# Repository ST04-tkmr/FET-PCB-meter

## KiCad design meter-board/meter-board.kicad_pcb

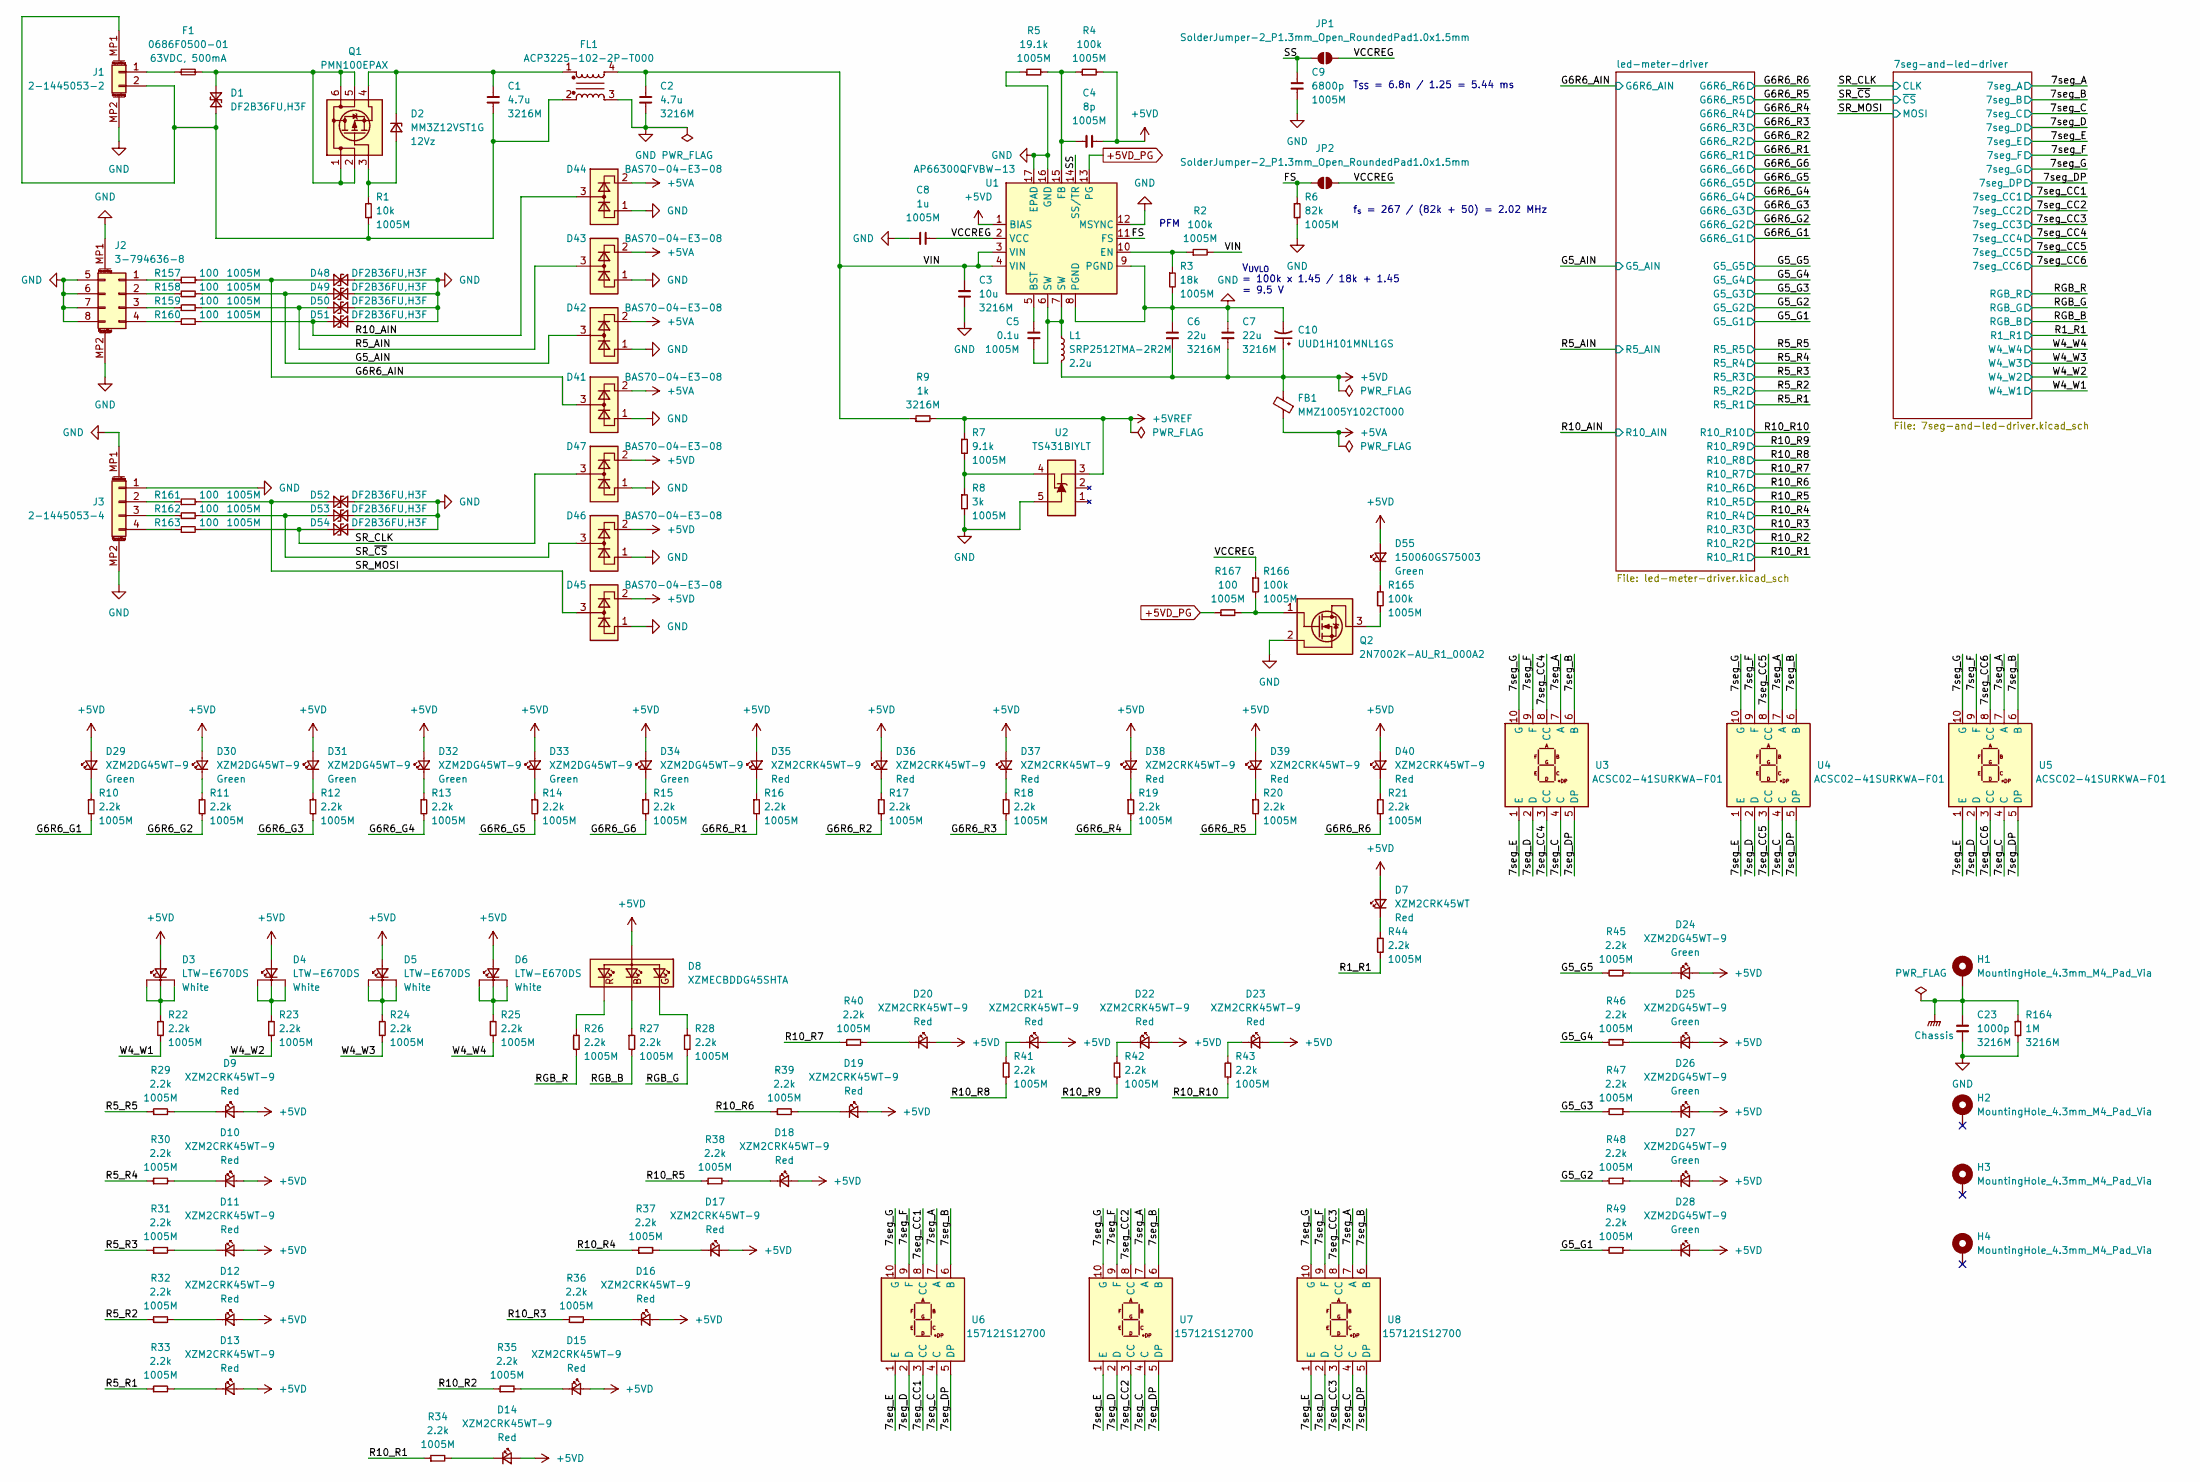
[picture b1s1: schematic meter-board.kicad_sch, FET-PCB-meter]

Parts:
C1, C2: 4.7u; C_1206_3216M
C3: 10u; C_1206_3216M
C4: 8p; C_0402_1005M
C5: 0.1u; C_0402_1005M
C6, C7: 22u; C_1206_3216M
C8: 1u; C_0402_1005M
C9: 6800p; C_0402_1005M
C10: UUD1H101MNL1GS; DigikeyPN 493-2306-1-ND
C23: 1000p; C_1206_3216M
D1, D48, D49, D50, D51, D52, D53, D54: DF2B36FU,H3F; DigikeyPN DF2B36FUH3FCT-ND
D2: MM3Z12VST1G; DigikeyPN MM3Z12VST1GOSCT-ND
D3, D4, D5, D6: LTW-E670DS; DigikeyPN 160-1766-1-ND
D7: XZM2CRK45WT; DigikeyPN 1497-1322-1-ND
D8: XZMECBDDG45SHTA; DigikeyPN 1497-XZMECBDDG45SHTACT-ND
D9, D10, D11, D12, D13, D14, D15, D16, D17, D18, D19, D20, D21, D22, D23, D35, D36, D37, D38, D39, D40: XZM2CRK45WT-9; DigikeyPN 1497-1332-1-ND
D24, D25, D26, D27, D28, D29, D30, D31, D32, D33, D34: XZM2DG45WT-9; DigikeyPN 1497-1338-1-ND
D41, D42, D43, D44, D45, D46, D47: BAS70-04-E3-08; DigikeyPN BAS70-04-E3-08CT-ND
D55: 150060GS75003; DigikeyPN 732-150060GS75003CT-ND
F1: 0686F0500-01; DigikeyPN 5923-0686F0500-01CT-ND
FB1: MMZ1005Y102CT000; DigikeyPN 445-2157-1-ND
FL1: ACP3225-102-2P-T000; DigikeyPN 445-8637-1-ND
H1, H2, H3, H4: MountingHole_4.3mm_M4_Pad_Via
J1: 2-1445053-2; DigikeyPN A33199CT-ND
J2: 3-794636-8; DigikeyPN A33238CT-ND
J3: 2-1445053-4; DigikeyPN A33201CT-ND
JP1, JP2: SolderJumper-2_P1.3mm_Open_RoundedPad1.0x1.5mm
L1: SRP2512TMA-2R2M; DigikeyPN 118-SRP2512TMA-2R2MCT-ND
Q1: PMN100EPAX; DigikeyPN 1727-PMN100EPAXCT-ND
Q2: 2N7002K-AU_R1_000A2; DigikeyPN 3757-2N7002K-AU_R1_000A2CT-ND
R1: 10k; R_0402_1005M
R2, R4, R165, R166: 100k; R_0402_1005M
R3: 18k; R_0402_1005M
R5: 19.1k; R_0402_1005M
R6: 82k; R_0402_1005M
R7: 9.1k; R_0402_1005M
R8: 3k; R_0402_1005M
R9: 1k; R_1206_3216M
R10, R11, R12, R13, R14, R15, R16, R17, R18, R19, R20, R21, R22, R23, R24, R25, R26, R27, R28, R29, R30, R31, R32, R33, R34, R35, R36, R37, R38, R39, R40, R41, R42, R43, R44, R45, R46, R47, R48, R49: 2.2k; R_0402_1005M
R157, R158, R159, R160, R161, R162, R163, R167: 100; R_0402_1005M
R164: 1M; R_1206_3216M
U1: AP66300QFVBW-13; DigikeyPN 31-AP66300QFVBW-13CT-ND
U2: TS431BIYLT; DigikeyPN 497-10248-1-ND
U3, U4, U5: ACSC02-41SURKWA-F01; DigikeyPN 754-1405-1-ND
U6, U7, U8: 157121S12700; DigikeyPN 732-157121S12700CT-ND

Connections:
+5VA: D41.2 (K), D42.2 (K), D43.2 (K), D44.2 (K), FB1.1; also elsewhere on the board
+5VD: C4.2, C6.2, C7.2, C10.1, D3.2 (A), D4.2 (A), D5.2 (A), D6.2 (A), D7.1 (A), D8.2 (A), D9.2 (A), D10.2 (A), D11.2 (A), D12.2 (A), D13.2 (A), D14.2 (A), D15.2 (A), D16.2 (A), D17.2 (A), D18.2 (A), D19.2 (A), D20.2 (A), D21.2 (A), D22.2 (A), D23.2 (A), D24.1 (A), D25.1 (A), D26.1 (A), D27.1 (A), D28.1 (A), D29.1 (A), D30.1 (A), D31.1 (A), D32.1 (A), D33.1 (A), D34.1 (A), D35.2 (A), D36.2 (A), D37.2 (A), D38.2 (A), D39.2 (A), D40.2 (A), D45.2 (K), D46.2 (K), D47.2 (K), D55.1 (A), FB1.2, L1.2, R4.2, U1.1 (BIAS); also elsewhere on the board
+5VD_PG: R167.1, U1.13 (PG)
+5VREF: R7.1, R9.2, U2.3 (K); also elsewhere on the board
/7seg_A: U3.7 (A), U4.7 (A), U5.7 (A), U6.7 (A), U7.7 (A), U8.7 (A); also elsewhere on the board
/7seg_B: U3.6 (B), U4.6 (B), U5.6 (B), U6.6 (B), U7.6 (B), U8.6 (B); also elsewhere on the board
/7seg_C: U3.4 (C), U4.4 (C), U5.4 (C), U6.4 (C), U7.4 (C), U8.4 (C); also elsewhere on the board
/7seg_CC1: U6.3 (CC), U6.8 (CC); also elsewhere on the board
/7seg_CC2: U7.3 (CC), U7.8 (CC); also elsewhere on the board
/7seg_CC3: U8.3 (CC), U8.8 (CC); also elsewhere on the board
/7seg_CC4: U3.3 (CC), U3.8 (CC); also elsewhere on the board
/7seg_CC5: U4.3 (CC), U4.8 (CC); also elsewhere on the board
/7seg_CC6: U5.3 (CC), U5.8 (CC); also elsewhere on the board
/7seg_D: U3.2 (D), U4.2 (D), U5.2 (D), U6.2 (D), U7.2 (D), U8.2 (D); also elsewhere on the board
/7seg_DP: U3.5 (DP), U4.5 (DP), U5.5 (DP), U6.5 (DP), U7.5 (DP), U8.5 (DP); also elsewhere on the board
/7seg_E: U3.1 (E), U4.1 (E), U5.1 (E), U6.1 (E), U7.1 (E), U8.1 (E); also elsewhere on the board
/7seg_F: U3.9 (F), U4.9 (F), U5.9 (F), U6.9 (F), U7.9 (F), U8.9 (F); also elsewhere on the board
/7seg_G: U3.10 (G), U4.10 (G), U5.10 (G), U6.10 (G), U7.10 (G), U8.10 (G); also elsewhere on the board
/FS: JP2.1 (A), R6.1, U1.11 (FS)
/G5_AIN: D42.3 (C), D49.1 (A1), R158.2; also elsewhere on the board
/G5_G1: R49.2; also elsewhere on the board
/G5_G2: R48.2; also elsewhere on the board
/G5_G3: R47.2; also elsewhere on the board
/G5_G4: R46.2; also elsewhere on the board
/G5_G5: R45.2; also elsewhere on the board
/G6R6_AIN: D41.3 (C), D48.1 (A1), R157.2; also elsewhere on the board
/G6R6_G1: R10.2; also elsewhere on the board
/G6R6_G2: R11.2; also elsewhere on the board
/G6R6_G3: R12.2; also elsewhere on the board
/G6R6_G4: R13.2; also elsewhere on the board
/G6R6_G5: R14.2; also elsewhere on the board
/G6R6_G6: R15.2; also elsewhere on the board
/G6R6_R1: R16.2; also elsewhere on the board
/G6R6_R2: R17.2; also elsewhere on the board
/G6R6_R3: R18.2; also elsewhere on the board
/G6R6_R4: R19.2; also elsewhere on the board
/G6R6_R5: R20.2; also elsewhere on the board
/G6R6_R6: R21.2; also elsewhere on the board
/R1_R1: R44.2; also elsewhere on the board
/R5_AIN: D43.3 (C), D50.1 (A1), R159.2; also elsewhere on the board
/R5_R1: R33.1; also elsewhere on the board
/R5_R2: R32.1; also elsewhere on the board
/R5_R3: R31.1; also elsewhere on the board
/R5_R4: R30.1; also elsewhere on the board
/R5_R5: R29.1; also elsewhere on the board
/R10_AIN: D44.3 (C), D51.1 (A1), R160.2; also elsewhere on the board
/R10_R1: R34.1; also elsewhere on the board
/R10_R2: R35.1; also elsewhere on the board
/R10_R3: R36.1; also elsewhere on the board
/R10_R4: R37.1; also elsewhere on the board
/R10_R5: R38.1; also elsewhere on the board
/R10_R6: R39.1; also elsewhere on the board
/R10_R7: R40.1; also elsewhere on the board
/R10_R8: R41.1; also elsewhere on the board
/R10_R9: R42.1; also elsewhere on the board
/R10_R10: R43.1; also elsewhere on the board
/RGB_B: R27.2; also elsewhere on the board
/RGB_G: R28.2; also elsewhere on the board
/RGB_R: R26.2; also elsewhere on the board
/SR_CLK: D47.3 (C), D54.1 (A1), R163.2; also elsewhere on the board
/SR_MOSI: D45.3 (C), D52.1 (A1), R161.2; also elsewhere on the board
/SR_~CS: D46.3 (C), D53.1 (A1), R162.2; also elsewhere on the board
/SS: C9.2, JP1.1 (A), U1.14 (SS/TR)
/VCCREG: C8.2, JP1.2 (B), JP2.2 (B), R166.1, U1.2 (VCC)
/VIN: C2.1, C3.1, FL1.4, R2.2, R9.1, U1.3 (VIN), U1.4 (VIN)
/W4_W1: R22.2; also elsewhere on the board
/W4_W2: R23.2; also elsewhere on the board
/W4_W3: R24.2; also elsewhere on the board
/W4_W4: R25.2; also elsewhere on the board
Chassis: C23.1, H1.MP, R164.1
GND: C2.2, C3.2, C6.1, C7.1, C8.1, C9.1, C10.2, C23.2, D41.1 (A), D42.1 (A), D43.1 (A), D44.1 (A), D45.1 (A), D46.1 (A), D47.1 (A), D48.2 (A2), D49.2 (A2), D50.2 (A2), D51.2 (A2), D52.2 (A2), D53.2 (A2), D54.2 (A2), FL1.3, J1.MP2 (MountPin), J2.5, J2.6, J2.7, J2.8, J2.MP1 (MountPin), J2.MP2 (MountPin), J3.1, J3.MP1 (MountPin), J3.MP2 (MountPin), Q2.2 (S), R3.2, R5.1, R6.2, R8.2, R164.2, U1.8 (PGND), U1.9 (PGND), U1.12 (MSYNC), U1.16 (GND), U1.17 (EPAD), U2.5 (A); also elsewhere on the board
unnamed: C5.1, L1.1, U1.6 (SW), U1.7 (SW)
unnamed: D1.1 (A1), F1.2, Q1.1 (D), Q1.2 (D), Q1.5 (D), Q1.6 (D)
unnamed: C1.2, D1.2 (A2), FL1.2, J1.2, J1.MP1 (MountPin), R1.1
unnamed: D2.2 (A), Q1.3 (G), R1.2
unnamed: C1.1, D2.1 (K), FL1.1, Q1.4 (S)
unnamed: D3.1 (K), D3.3 (K), D3.4 (K), R22.1
unnamed: D4.1 (K), D4.3 (K), D4.4 (K), R23.1
unnamed: D5.1 (K), D5.3 (K), D5.4 (K), R24.1
unnamed: D6.1 (K), D6.3 (K), D6.4 (K), R25.1
unnamed: D7.2 (K), R44.1
unnamed: D8.3 (B_K), R27.1
unnamed: D8.4 (G_K), R28.1
unnamed: D8.1 (R_K), R26.1
unnamed: D9.1 (K), R29.2
unnamed: D10.1 (K), R30.2
unnamed: D11.1 (K), R31.2
unnamed: D12.1 (K), R32.2
unnamed: D13.1 (K), R33.2
unnamed: D14.1 (K), R34.2
unnamed: D15.1 (K), R35.2
unnamed: D16.1 (K), R36.2
unnamed: D17.1 (K), R37.2
unnamed: D18.1 (K), R38.2
unnamed: D19.1 (K), R39.2
unnamed: D20.1 (K), R40.2
unnamed: D21.1 (K), R41.2
unnamed: D22.1 (K), R42.2
unnamed: D23.1 (K), R43.2
unnamed: D24.2 (K), R45.1
unnamed: D25.2 (K), R46.1
unnamed: D26.2 (K), R47.1
unnamed: D27.2 (K), R48.1
unnamed: D28.2 (K), R49.1
unnamed: D29.2 (K), R10.1
unnamed: D30.2 (K), R11.1
unnamed: D31.2 (K), R12.1
unnamed: D32.2 (K), R13.1
unnamed: D33.2 (K), R14.1
unnamed: D34.2 (K), R15.1
unnamed: D35.1 (K), R16.1
unnamed: D36.1 (K), R17.1
unnamed: D37.1 (K), R18.1
unnamed: D38.1 (K), R19.1
unnamed: D39.1 (K), R20.1
unnamed: D40.1 (K), R21.1
unnamed: D55.2 (K), R165.1
unnamed: F1.1, J1.1
unnamed: J2.1, R157.1
unnamed: J2.2, R158.1
unnamed: J2.3, R159.1
unnamed: J2.4, R160.1
unnamed: J3.2, R161.1
unnamed: J3.3, R162.1
unnamed: J3.4, R163.1
unnamed: Q2.3 (D), R165.2
unnamed: Q2.1 (G), R166.2, R167.2
unnamed: C5.2, U1.5 (BST)
unnamed: R2.1, R3.1, U1.10 (EN)
unnamed: C4.1, R4.1, R5.2, U1.15 (FB)
unnamed: R7.2, R8.1, U2.4 (REF)

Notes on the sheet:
V_{UVLO} = 100k x 1.45 / 18k + 1.45 = 9.5 V
PFM
f_{s} = 267 / (82k + 50) = 2.02 MHz
T_{SS} = 6.8n / 1.25 = 5.44 ms

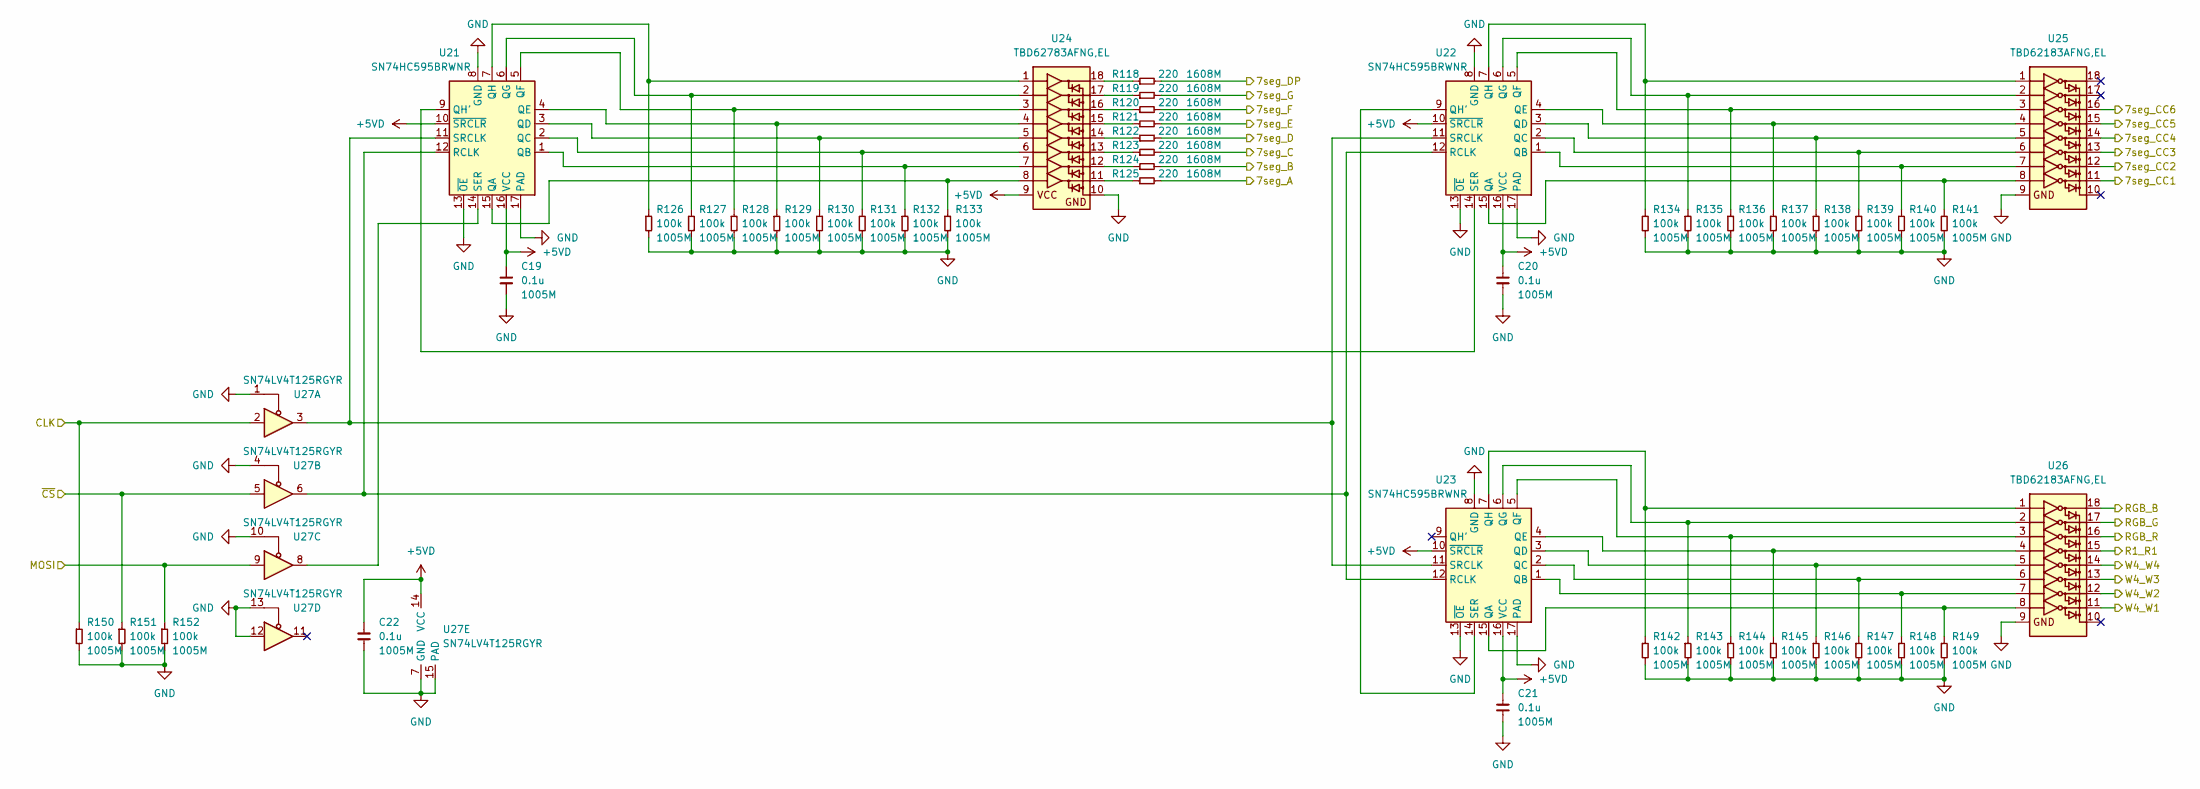
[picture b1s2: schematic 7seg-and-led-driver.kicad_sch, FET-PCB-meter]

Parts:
C19, C20, C21, C22: 0.1u; C_1005M
R118, R119, R120, R121, R122, R123, R124, R125: 220; R_0603_1608M
R126, R127, R128, R129, R130, R131, R132, R133, R134, R135, R136, R137, R138, R139, R140, R141, R142, R143, R144, R145, R146, R147, R148, R149, R150, R151, R152: 100k; R_0402_1005M
U21, U22, U23: SN74HC595BRWNR; DigikeyPN 296-44070-1-ND
U24: TBD62783AFNG,EL; DigikeyPN TBD62783AFNGELCT-ND
U25, U26: TBD62183AFNG,EL; DigikeyPN TBD62183AFNGELCT-ND
U27: SN74LV4T125RGYR; DigikeyPN 296-40546-1-ND

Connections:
+5VD: C19.1, C20.1, C21.1, C22.1, U21.10 (~SRCLR), U21.16 (VCC), U22.10 (~SRCLR), U22.16 (VCC), U23.10 (~SRCLR), U23.16 (VCC), U24.9 (VCC), U27.14 (VCC); also elsewhere on the board
/7seg_A: R125.2; also elsewhere on the board
/7seg_B: R124.2; also elsewhere on the board
/7seg_C: R123.2; also elsewhere on the board
/7seg_CC1: U25.11 (O8); also elsewhere on the board
/7seg_CC2: U25.12 (O7); also elsewhere on the board
/7seg_CC3: U25.13 (O6); also elsewhere on the board
/7seg_CC4: U25.14 (O5); also elsewhere on the board
/7seg_CC5: U25.15 (O4); also elsewhere on the board
/7seg_CC6: U25.16 (O3); also elsewhere on the board
/7seg_D: R122.2; also elsewhere on the board
/7seg_DP: R118.2; also elsewhere on the board
/7seg_E: R121.2; also elsewhere on the board
/7seg_F: R120.2; also elsewhere on the board
/7seg_G: R119.2; also elsewhere on the board
/R1_R1: U26.15 (O4); also elsewhere on the board
/RGB_B: U26.18 (O1); also elsewhere on the board
/RGB_G: U26.17 (O2); also elsewhere on the board
/RGB_R: U26.16 (O3); also elsewhere on the board
/SR_CLK: R150.1, U27.2; also elsewhere on the board
/SR_MOSI: R152.1, U27.9; also elsewhere on the board
/SR_~CS: R151.1, U27.5; also elsewhere on the board
/W4_W1: U26.11 (O8); also elsewhere on the board
/W4_W2: U26.12 (O7); also elsewhere on the board
/W4_W3: U26.13 (O6); also elsewhere on the board
/W4_W4: U26.14 (O5); also elsewhere on the board
GND: C19.2, C20.2, C21.2, C22.2, R126.2, R127.2, R128.2, R129.2, R130.2, R131.2, R132.2, R133.2, R134.2, R135.2, R136.2, R137.2, R138.2, R139.2, R140.2, R141.2, R142.2, R143.2, R144.2, R145.2, R146.2, R147.2, R148.2, R149.2, R150.2, R151.2, R152.2, U21.8 (GND), U21.13 (~OE), U21.17 (PAD), U22.8 (GND), U22.13 (~OE), U22.17 (PAD), U23.8 (GND), U23.13 (~OE), U23.17 (PAD), U24.10 (GND), U25.9 (GND), U26.9 (GND), U27.1, U27.4, U27.7 (GND), U27.10, U27.12, U27.13, U27.15 (PAD); also elsewhere on the board
unnamed: R133.1, U21.15 (QA), U24.8 (I8)
unnamed: R132.1, U21.1 (QB), U24.7 (I7)
unnamed: R131.1, U21.2 (QC), U24.6 (I6)
unnamed: R130.1, U21.3 (QD), U24.5 (I5)
unnamed: R129.1, U21.4 (QE), U24.4 (I4)
unnamed: R128.1, U21.5 (QF), U24.3 (I3)
unnamed: R127.1, U21.6 (QG), U24.2 (I2)
unnamed: U21.9 (QH'), U22.14 (SER)
unnamed: R126.1, U21.7 (QH), U24.1 (I1)
unnamed: U21.12 (RCLK), U22.12 (RCLK), U23.12 (RCLK), U27.6
unnamed: U21.14 (SER), U27.8
unnamed: U21.11 (SRCLK), U22.11 (SRCLK), U23.11 (SRCLK), U27.3
unnamed: R141.1, U22.15 (QA), U25.8 (I8)
unnamed: R140.1, U22.1 (QB), U25.7 (I7)
unnamed: R139.1, U22.2 (QC), U25.6 (I6)
unnamed: R138.1, U22.3 (QD), U25.5 (I5)
unnamed: R137.1, U22.4 (QE), U25.4 (I4)
unnamed: R136.1, U22.5 (QF), U25.3 (I3)
unnamed: R135.1, U22.6 (QG), U25.2 (I2)
unnamed: U22.9 (QH'), U23.14 (SER)
unnamed: R134.1, U22.7 (QH), U25.1 (I1)
unnamed: R149.1, U23.15 (QA), U26.8 (I8)
unnamed: R148.1, U23.1 (QB), U26.7 (I7)
unnamed: R147.1, U23.2 (QC), U26.6 (I6)
unnamed: R146.1, U23.3 (QD), U26.5 (I5)
unnamed: R145.1, U23.4 (QE), U26.4 (I4)
unnamed: R144.1, U23.5 (QF), U26.3 (I3)
unnamed: R143.1, U23.6 (QG), U26.2 (I2)
unnamed: R142.1, U23.7 (QH), U26.1 (I1)
unnamed: R118.1, U24.18 (O1)
unnamed: R119.1, U24.17 (O2)
unnamed: R120.1, U24.16 (O3)
unnamed: R121.1, U24.15 (O4)
unnamed: R122.1, U24.14 (O5)
unnamed: R123.1, U24.13 (O6)
unnamed: R124.1, U24.12 (O7)
unnamed: R125.1, U24.11 (O8)

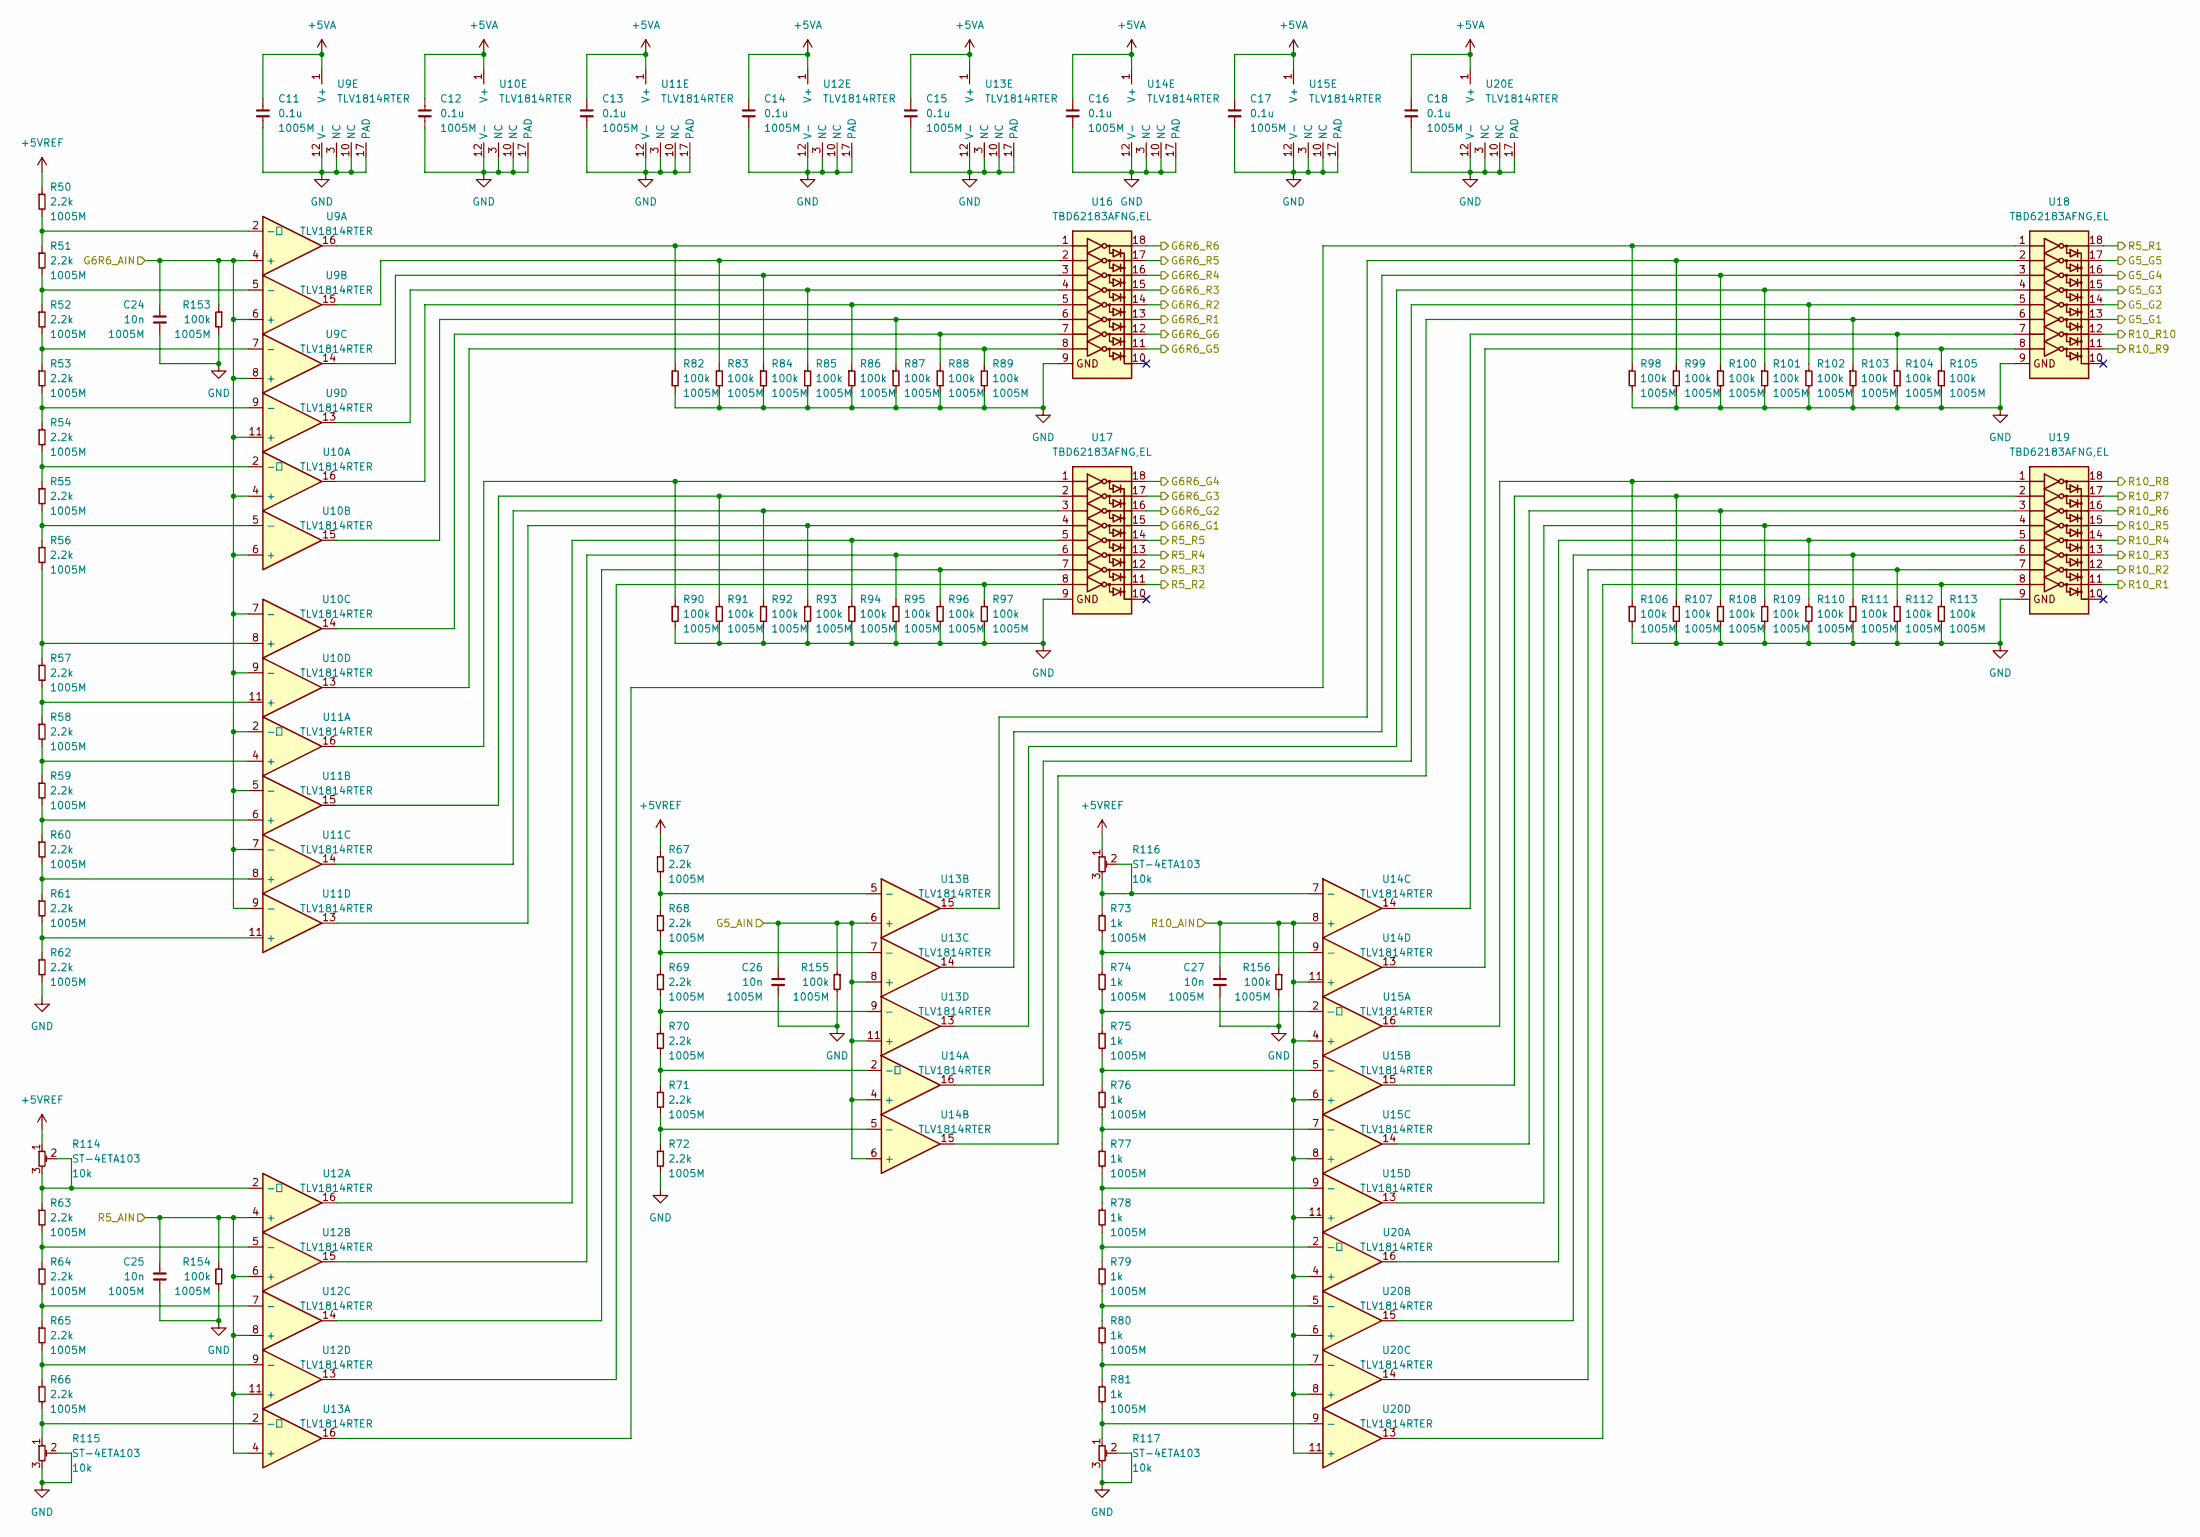
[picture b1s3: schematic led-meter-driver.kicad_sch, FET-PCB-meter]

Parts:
C11, C12, C13, C14, C15, C16, C17, C18: 0.1u; C_0402_1005M
C24, C25, C26, C27: 10n; C_0402_1005M
R50, R51, R52, R53, R54, R55, R56, R57, R58, R59, R60, R61, R62, R63, R64, R65, R66, R67, R68, R69, R70, R71, R72: 2.2k; R_0402_1005M
R73, R74, R75, R76, R77, R78, R79, R80, R81: 1k; R_0402_1005M
R82, R83, R84, R85, R86, R87, R88, R89, R90, R91, R92, R93, R94, R95, R96, R97, R98, R99, R100, R101, R102, R103, R104, R105, R106, R107, R108, R109, R110, R111, R112, R113, R153, R154, R155, R156: 100k; R_0402_1005M
R114, R115, R116, R117: ST-4ETA103; DigikeyPN 563-ST-4ETA103CT-ND
U9, U10, U11, U12, U13, U14, U15, U20: TLV1814RTER; DigikeyPN 296-TLV1814RTERCT-ND
U16, U17, U18, U19: TBD62183AFNG,EL; DigikeyPN TBD62183AFNGELCT-ND

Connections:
+5VA: C11.1, C12.1, C13.1, C14.1, C15.1, C16.1, C17.1, C18.1, U9.1 (V+), U10.1 (V+), U11.1 (V+), U12.1 (V+), U13.1 (V+), U14.1 (V+), U15.1 (V+), U20.1 (V+); also elsewhere on the board
+5VREF: R50.1, R67.1, R114.1, R116.1; also elsewhere on the board
/G5_AIN: C26.1, R155.1, U13.6 (+), U13.8 (+), U13.11 (+), U14.4 (+), U14.6 (+); also elsewhere on the board
/G5_G1: U18.13 (O6); also elsewhere on the board
/G5_G2: U18.14 (O5); also elsewhere on the board
/G5_G3: U18.15 (O4); also elsewhere on the board
/G5_G4: U18.16 (O3); also elsewhere on the board
/G5_G5: U18.17 (O2); also elsewhere on the board
/G6R6_AIN: C24.1, R153.1, U9.4 (+), U9.6 (+), U9.8 (+), U9.11 (+), U10.4 (+), U10.6 (+), U10.7 (-), U10.9 (-), U11.2 (-), U11.5 (-), U11.7 (-), U11.9 (-); also elsewhere on the board
/G6R6_G1: U17.15 (O4); also elsewhere on the board
/G6R6_G2: U17.16 (O3); also elsewhere on the board
/G6R6_G3: U17.17 (O2); also elsewhere on the board
/G6R6_G4: U17.18 (O1); also elsewhere on the board
/G6R6_G5: U16.11 (O8); also elsewhere on the board
/G6R6_G6: U16.12 (O7); also elsewhere on the board
/G6R6_R1: U16.13 (O6); also elsewhere on the board
/G6R6_R2: U16.14 (O5); also elsewhere on the board
/G6R6_R3: U16.15 (O4); also elsewhere on the board
/G6R6_R4: U16.16 (O3); also elsewhere on the board
/G6R6_R5: U16.17 (O2); also elsewhere on the board
/G6R6_R6: U16.18 (O1); also elsewhere on the board
/R5_AIN: C25.1, R154.1, U12.4 (+), U12.6 (+), U12.8 (+), U12.11 (+), U13.4 (+); also elsewhere on the board
/R5_R1: U18.18 (O1); also elsewhere on the board
/R5_R2: U17.11 (O8); also elsewhere on the board
/R5_R3: U17.12 (O7); also elsewhere on the board
/R5_R4: U17.13 (O6); also elsewhere on the board
/R5_R5: U17.14 (O5); also elsewhere on the board
/R10_AIN: C27.1, R156.1, U14.8 (+), U14.11 (+), U15.4 (+), U15.6 (+), U15.8 (+), U15.11 (+), U20.4 (+), U20.6 (+), U20.8 (+), U20.11 (+); also elsewhere on the board
/R10_R1: U19.11 (O8); also elsewhere on the board
/R10_R2: U19.12 (O7); also elsewhere on the board
/R10_R3: U19.13 (O6); also elsewhere on the board
/R10_R4: U19.14 (O5); also elsewhere on the board
/R10_R5: U19.15 (O4); also elsewhere on the board
/R10_R6: U19.16 (O3); also elsewhere on the board
/R10_R7: U19.17 (O2); also elsewhere on the board
/R10_R8: U19.18 (O1); also elsewhere on the board
/R10_R9: U18.11 (O8); also elsewhere on the board
/R10_R10: U18.12 (O7); also elsewhere on the board
GND: C11.2, C12.2, C13.2, C14.2, C15.2, C16.2, C17.2, C18.2, C24.2, C25.2, C26.2, C27.2, R62.2, R72.2, R82.2, R83.2, R84.2, R85.2, R86.2, R87.2, R88.2, R89.2, R90.2, R91.2, R92.2, R93.2, R94.2, R95.2, R96.2, R97.2, R98.2, R99.2, R100.2, R101.2, R102.2, R103.2, R104.2, R105.2, R106.2, R107.2, R108.2, R109.2, R110.2, R111.2, R112.2, R113.2, R115.2, R115.3, R117.2, R117.3, R153.2, R154.2, R155.2, R156.2, U9.3 (NC), U9.10 (NC), U9.12 (V-), U9.17 (PAD), U10.3 (NC), U10.10 (NC), U10.12 (V-), U10.17 (PAD), U11.3 (NC), U11.10 (NC), U11.12 (V-), U11.17 (PAD), U12.3 (NC), U12.10 (NC), U12.12 (V-), U12.17 (PAD), U13.3 (NC), U13.10 (NC), U13.12 (V-), U13.17 (PAD), U14.3 (NC), U14.10 (NC), U14.12 (V-), U14.17 (PAD), U15.3 (NC), U15.10 (NC), U15.12 (V-), U15.17 (PAD), U16.9 (GND), U17.9 (GND), U18.9 (GND), U19.9 (GND), U20.3 (NC), U20.10 (NC), U20.12 (V-), U20.17 (PAD); also elsewhere on the board
unnamed: R50.2, R51.1, U9.2 (-)
unnamed: R51.2, R52.1, U9.5 (-)
unnamed: R52.2, R53.1, U9.7 (-)
unnamed: R53.2, R54.1, U9.9 (-)
unnamed: R54.2, R55.1, U10.2 (-)
unnamed: R55.2, R56.1, U10.5 (-)
unnamed: R56.2, R57.1, U10.8 (+)
unnamed: R57.2, R58.1, U10.11 (+)
unnamed: R58.2, R59.1, U11.4 (+)
unnamed: R59.2, R60.1, U11.6 (+)
unnamed: R60.2, R61.1, U11.8 (+)
unnamed: R61.2, R62.1, U11.11 (+)
unnamed: R63.1, R114.2, R114.3, U12.2 (-)
unnamed: R63.2, R64.1, U12.5 (-)
unnamed: R64.2, R65.1, U12.7 (-)
unnamed: R65.2, R66.1, U12.9 (-)
unnamed: R66.2, R115.1, U13.2 (-)
unnamed: R67.2, R68.1, U13.5 (-)
unnamed: R68.2, R69.1, U13.7 (-)
unnamed: R69.2, R70.1, U13.9 (-)
unnamed: R70.2, R71.1, U14.2 (-)
unnamed: R71.2, R72.1, U14.5 (-)
unnamed: R73.1, R116.2, R116.3, U14.7 (-)
unnamed: R73.2, R74.1, U14.9 (-)
unnamed: R74.2, R75.1, U15.2 (-)
unnamed: R75.2, R76.1, U15.5 (-)
unnamed: R76.2, R77.1, U15.7 (-)
unnamed: R77.2, R78.1, U15.9 (-)
unnamed: R82.1, U9.16, U16.1 (I1)
unnamed: R83.1, U9.15, U16.2 (I2)
unnamed: R84.1, U9.14, U16.3 (I3)
unnamed: R85.1, U9.13, U16.4 (I4)
unnamed: R86.1, U10.16, U16.5 (I5)
unnamed: R87.1, U10.15, U16.6 (I6)
unnamed: R88.1, U10.14, U16.7 (I7)
unnamed: R89.1, U10.13, U16.8 (I8)
unnamed: R90.1, U11.16, U17.1 (I1)
unnamed: R91.1, U11.15, U17.2 (I2)
unnamed: R92.1, U11.14, U17.3 (I3)
unnamed: R93.1, U11.13, U17.4 (I4)
unnamed: R94.1, U12.16, U17.5 (I5)
unnamed: R95.1, U12.15, U17.6 (I6)
unnamed: R96.1, U12.14, U17.7 (I7)
unnamed: R97.1, U12.13, U17.8 (I8)
unnamed: R98.1, U13.16, U18.1 (I1)
unnamed: R99.1, U13.15, U18.2 (I2)
unnamed: R100.1, U13.14, U18.3 (I3)
unnamed: R101.1, U13.13, U18.4 (I4)
unnamed: R102.1, U14.16, U18.5 (I5)
unnamed: R103.1, U14.15, U18.6 (I6)
unnamed: R104.1, U14.14, U18.7 (I7)
unnamed: R105.1, U14.13, U18.8 (I8)
unnamed: R106.1, U15.16, U19.1 (I1)
unnamed: R107.1, U15.15, U19.2 (I2)
unnamed: R108.1, U15.14, U19.3 (I3)
unnamed: R109.1, U15.13, U19.4 (I4)
unnamed: R110.1, U19.5 (I5), U20.16
unnamed: R111.1, U19.6 (I6), U20.15
unnamed: R112.1, U19.7 (I7), U20.14
unnamed: R113.1, U19.8 (I8), U20.13
unnamed: R78.2, R79.1, U20.2 (-)
unnamed: R79.2, R80.1, U20.5 (-)
unnamed: R80.2, R81.1, U20.7 (-)
unnamed: R81.2, R117.1, U20.9 (-)

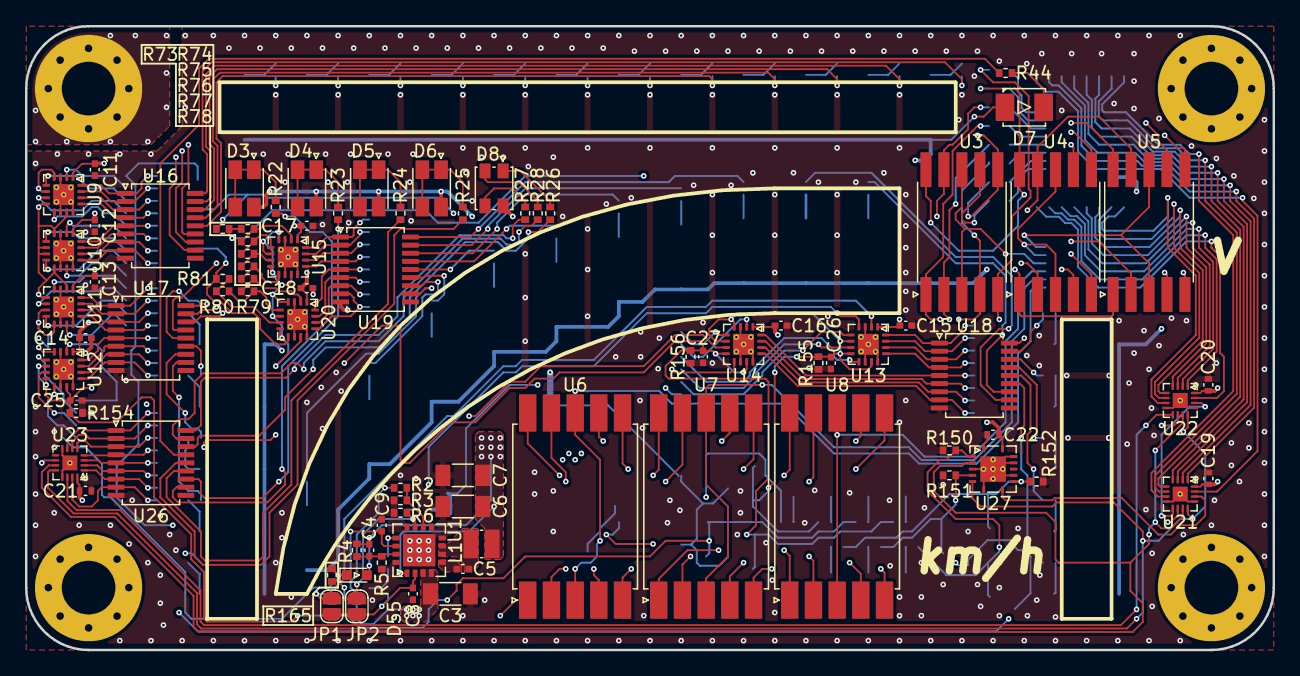
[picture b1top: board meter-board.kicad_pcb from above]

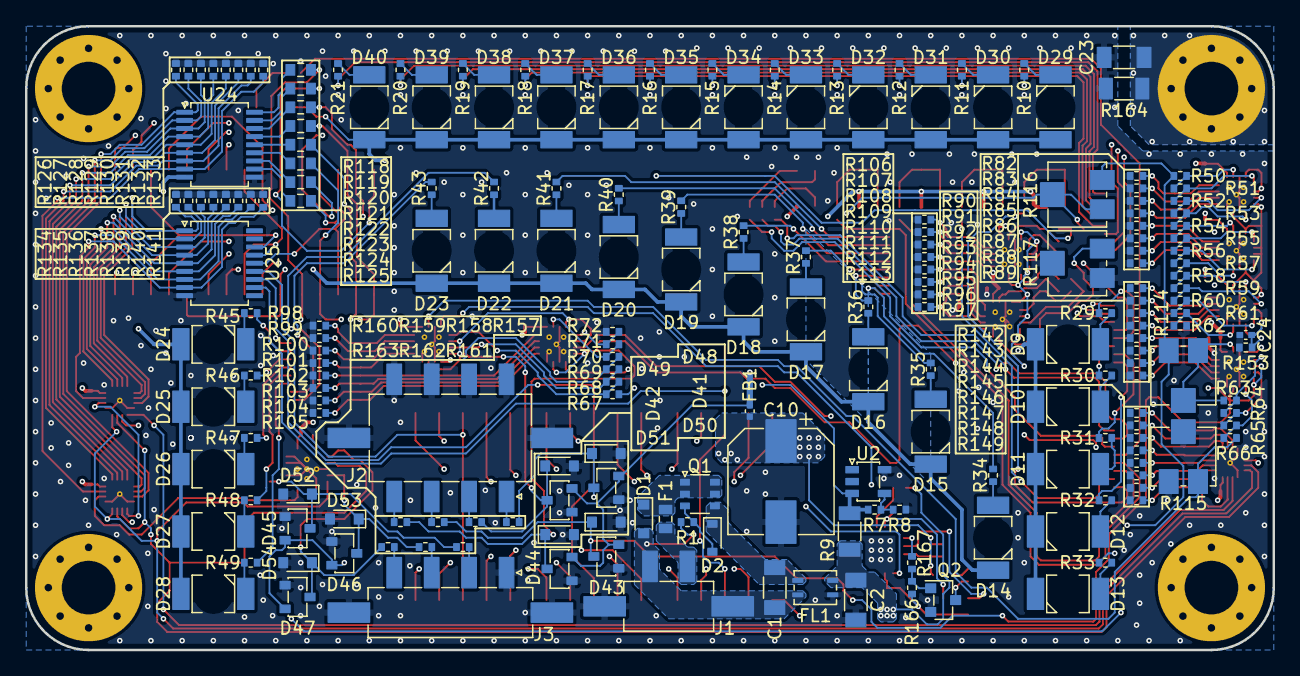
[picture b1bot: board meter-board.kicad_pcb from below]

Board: 4 copper layers, 100.0 x 50.0 mm, 291 parts (202 on the bottom side), 232 nets.

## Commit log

2025-06-24 create drawio project for UI design design released
2025-06-24 generate png
2025-06-24 create drawio project
2025-06-24 modification
2025-06-25 add blocks
2025-06-25 modify UI design
2025-06-25 create block diagram, still not power
2025-06-26 add power diagram
2025-06-26 create kicad project
2025-06-29 add title, revision
2025-07-04 add protection circuit
2025-07-05 add power circuit and LEDs
2025-07-05 add comparators for LED x 10
2025-07-05 generate pdf
2025-07-05 modified
2025-07-05 create a new sheet
2025-07-05 create a new sheet and add led drive circuits
2025-07-05 add new sheets and update circuits
2025-07-06 update circuits
2025-07-06 modify label
2025-07-06 add input filter
2025-07-06 completed designing circuit and checked DRC
2025-07-06 modify pcb config
2025-07-08 update layout
2025-07-10 layout of components is finished
2025-07-10 modify pwr line
2025-07-10 update wiring
2025-07-11 update AW
2025-07-12 update patterns
2025-07-13 modify net name
2025-07-27 finish wiring
2025-07-27 update silks
2025-07-30 modify wiring and update silks
2025-08-01 add vias, modify gnd pattern
2025-09-06 modify gnd-zone and add via
